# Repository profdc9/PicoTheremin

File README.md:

This is a theremin based on the "Bluepill" devboard with a STM32F103C8T6 microcontroller.
This material is copyrighted by Daniel Marks (KW4TI) and licensed under
the Creative Commons License CC-BY-SA 4.0.  Software is copyrighted using the zlib
open-source license.

It consists of three parts: 

MCTheremin directory - the stm32duino project

board - the PCB board in Kicad of the theremin.

genwaves - little octave script to generate the waveform data

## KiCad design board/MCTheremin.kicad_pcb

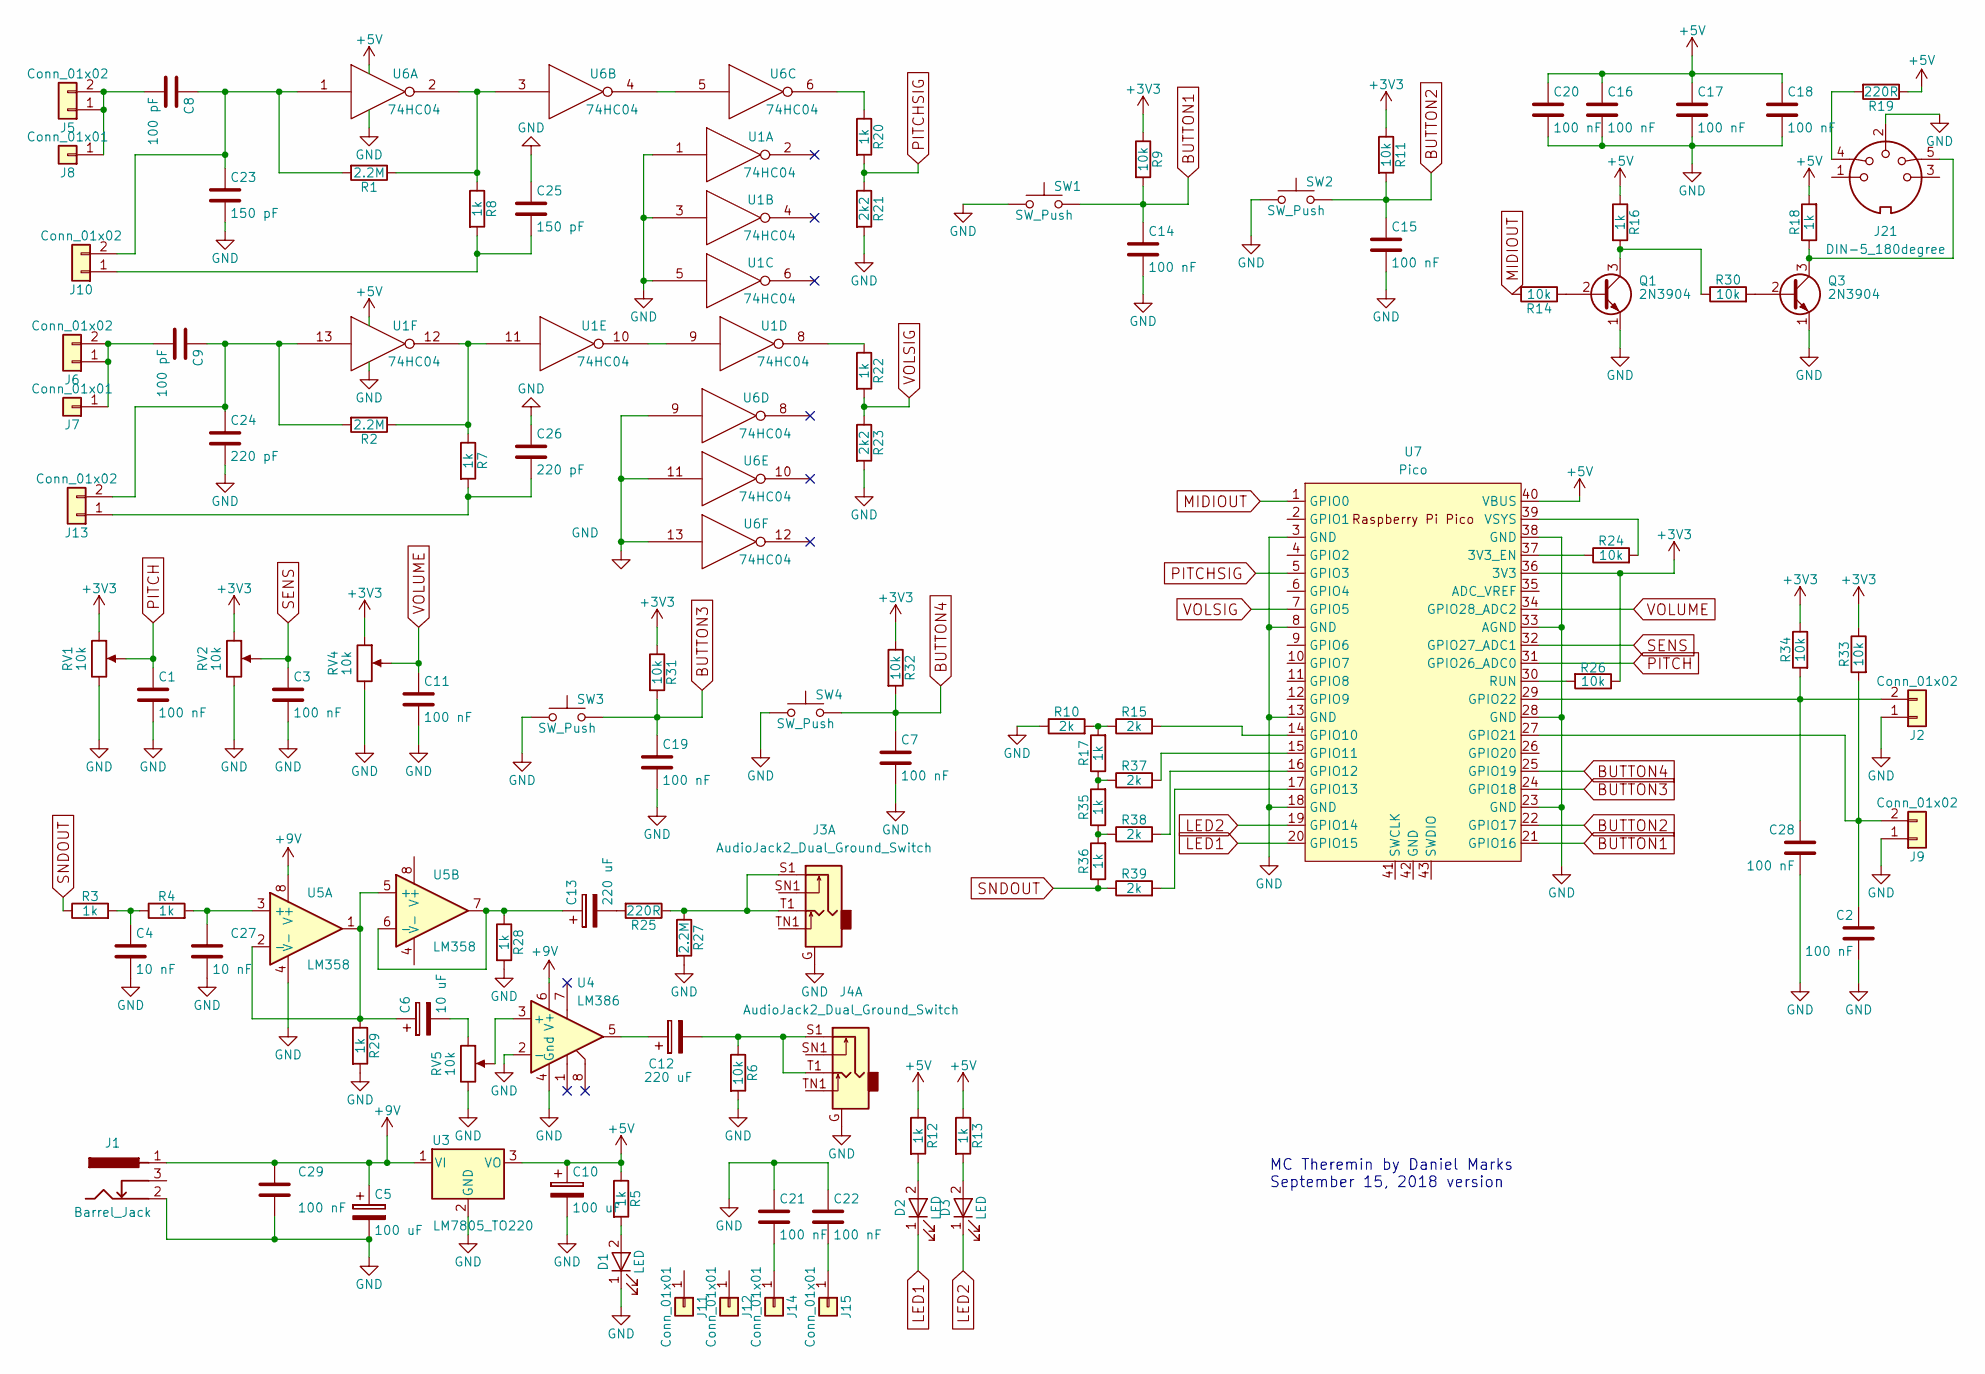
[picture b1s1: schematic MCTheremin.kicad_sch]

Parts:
C1, C2, C3, C7, C11, C14, C15, C16, C17, C18, C19, C20, C21, C22, C28, C29: 100 nF; C_Disc_D5.0mm_W2.5mm_P5.00mm
C4, C27: 10 nF; C_Disc_D5.0mm_W2.5mm_P5.00mm
C5, C10: 100 uF; CP_Radial_D5.0mm_P2.50mm
C6: 10 uF; CP_Radial_D5.0mm_P2.50mm
C8, C9: 100 pF; C_Disc_D5.0mm_W2.5mm_P5.00mm
C12, C13: 220 uF; CP_Radial_D5.0mm_P2.50mm
C23, C25: 150 pF; C_Disc_D5.0mm_W2.5mm_P5.00mm
C24, C26: 220 pF; C_Disc_D5.0mm_W2.5mm_P5.00mm
D1, D2, D3: LED; LED_D5.0mm
J1: Barrel_Jack; BARREL_JACK
J2, J5, J6, J9, J10, J13: Conn_01x02; TerminalBlock_bornier-2_P5.08mm
J3, J4: AudioJack2_Dual_Ground_Switch; PJ-3240-35mm-stereo
J7, J8, J11, J12, J14, J15: Conn_01x01; 1pin
J21: DIN-5_180degree; DIN5Circular
Q1, Q3: 2N3904; TO-92_Inline_Wide
R1, R2, R27: 2.2M; R_Axial_DIN0207_L6.3mm_D2.5mm_P7.62mm_Horizontal
R3, R4, R5, R7, R8, R12, R13, R16, R17, R18, R20, R22, R28, R29, R35, R36: 1k; R_Axial_DIN0207_L6.3mm_D2.5mm_P7.62mm_Horizontal
R6, R9, R11, R14, R24, R26, R30, R31, R32, R33, R34: 10k; R_Axial_DIN0207_L6.3mm_D2.5mm_P7.62mm_Horizontal
R10, R15, R37, R38, R39: 2k; R_Axial_DIN0207_L6.3mm_D2.5mm_P7.62mm_Horizontal
R19, R25: 220R; R_Axial_DIN0207_L6.3mm_D2.5mm_P7.62mm_Horizontal
R21, R23: 2k2; R_Axial_DIN0207_L6.3mm_D2.5mm_P7.62mm_Horizontal
RV1, RV2, RV4, RV5: 10k; Potentiometer_Big_Small_Combined
SW1, SW2, SW3, SW4: SW_Push; SW_PUSH_6mm
U1, U6: 74HC04; DIP-14_W7.62mm_Socket
U3: LM7805_TO220; TO-220-3_Vertical
U4: LM386; DIP-8_W7.62mm_Socket
U5: LM358; DIP-8_W7.62mm_Socket
U7: Pico; RPi_Pico_SMD_TH

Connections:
+3V3: R9.1, R11.1, R26.1, R31.1, R32.1, R33.1, R34.1, RV1.1, RV2.1, RV4.1, U7.36 (3V3)
+5V: C10.1, C16.1, C17.1, C18.1, C20.1, R5.1, R12.1, R13.1, R16.1, R18.2, R19.1, U1.14 (VCC), U3.3 (VO), U6.14 (VCC), U7.40 (VBUS)
+9V: C5.1, C29.1, J1.1, U3.1 (VI), U4.6 (V+), U5.8 (V+)
BUTTON1: C14.1, R9.2, SW1.2, U7.21 (GPIO16)
BUTTON2: C15.1, R11.2, SW2.2, U7.22 (GPIO17)
BUTTON3: C19.1, R31.2, SW3.2, U7.24 (GPIO18)
BUTTON4: C7.1, R32.2, SW4.2, U7.25 (GPIO19)
GND: C1.2, C2.2, C3.2, C4.2, C5.2, C7.2, C10.2, C11.2, C14.2, C15.2, C16.2, C17.2, C18.2, C19.2, C20.2, C21.1, C22.1, C23.2, C24.2, C25.1, C26.1, C27.2, C28.2, C29.2, D1.1 (K), J1.2, J2.1, J3.G, J4.G, J9.1, J21.2, Q1.1 (E), Q3.1 (E), R6.2, R10.1, R21.2, R23.2, R27.2, R28.2, R29.2, RV1.3, RV2.3, RV4.3, RV5.3, SW1.1, SW2.1, SW3.1, SW4.1, U1.1, U1.3, U1.5, U1.7 (GND), U3.2 (GND), U4.2 (-), U4.4 (Gnd), U5.4 (V-), U6.7 (GND), U6.9, U6.11, U6.13, U7.3 (GND), U7.8 (GND), U7.13 (GND), U7.18 (GND), U7.23 (GND), U7.28 (GND), U7.33 (AGND), U7.38 (GND)
LED1: D2.1 (K), U7.20 (GPIO15)
LED2: D3.1 (K), U7.19 (GPIO14)
MIDIOUT: R14.2, U7.1 (GPIO0)
unnamed: C4.1, R3.2, R4.1
unnamed: C6.2, RV5.1
unnamed: C12.1, U4.5
unnamed: C12.2, J4.S1, J4.T1, R6.1
unnamed: C13.2, R25.2
unnamed: D1.2 (A), R5.2
unnamed: D2.2 (A), R12.2
unnamed: D3.2 (A), R13.2
unnamed: C28.1, J2.2, R34.2, U7.29 (GPIO22)
unnamed: J3.S1, J3.T1, R25.1, R27.1
unnamed: C8.2, J5.1, J5.2, J8.1
unnamed: C9.2, J6.1, J6.2, J7.1
unnamed: C2.1, J9.2, R33.2, U7.27 (GPIO21)
unnamed: C25.2, J10.1, R8.2
unnamed: C8.1, C23.1, J10.2, R1.2, U6.1
unnamed: C26.2, J13.1, R7.2
unnamed: C9.1, C24.1, J13.2, R2.2, U1.13
unnamed: C21.2, J14.1
unnamed: C22.2, J15.1
unnamed: J21.4, R19.2
unnamed: Q1.2 (B), R14.1
unnamed: Q1.3 (C), R16.2, R30.1
unnamed: Q3.2 (B), R30.2
unnamed: J21.5, Q3.3 (C), R18.1
unnamed: R1.1, R8.1, U6.2, U6.3
unnamed: R2.1, R7.1, U1.11, U1.12
unnamed: R10.2, R15.1, R17.2
unnamed: R17.1, R35.2, R37.1
unnamed: R20.1, U6.6
unnamed: R22.1, U1.8
unnamed: R35.1, R36.2, R38.1
unnamed: U1.9, U1.10
unnamed: RV5.2, U4.3 (+)
unnamed: C27.1, R4.2, U5.3 (+)
unnamed: C6.1, R29.1, U5.1, U5.2 (-), U5.5 (+)
unnamed: C13.1, R28.1, U5.6 (-), U5.7
unnamed: U6.4, U6.5
unnamed: R24.1, U7.37 (3V3_EN)
unnamed: R15.2, U7.14 (GPIO10)
unnamed: R37.2, U7.15 (GPIO11)
unnamed: R38.2, U7.16 (GPIO12)
unnamed: R39.2, U7.17 (GPIO13)
unnamed: R26.2, U7.30 (RUN)
unnamed: R24.2, U7.39 (VSYS)
PITCH: C1.1, RV1.2, U7.31 (GPIO26_ADC0)
PITCHSIG: R20.2, R21.1, U7.5 (GPIO3)
SENS: C3.1, RV2.2, U7.32 (GPIO27_ADC1)
SNDOUT: R3.1, R36.1, R39.1
VOLSIG: R22.2, R23.1, U7.7 (GPIO5)
VOLUME: C11.1, RV4.2, U7.34 (GPIO28_ADC2)

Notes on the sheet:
MC Theremin by Daniel Marks September 15, 2018 version

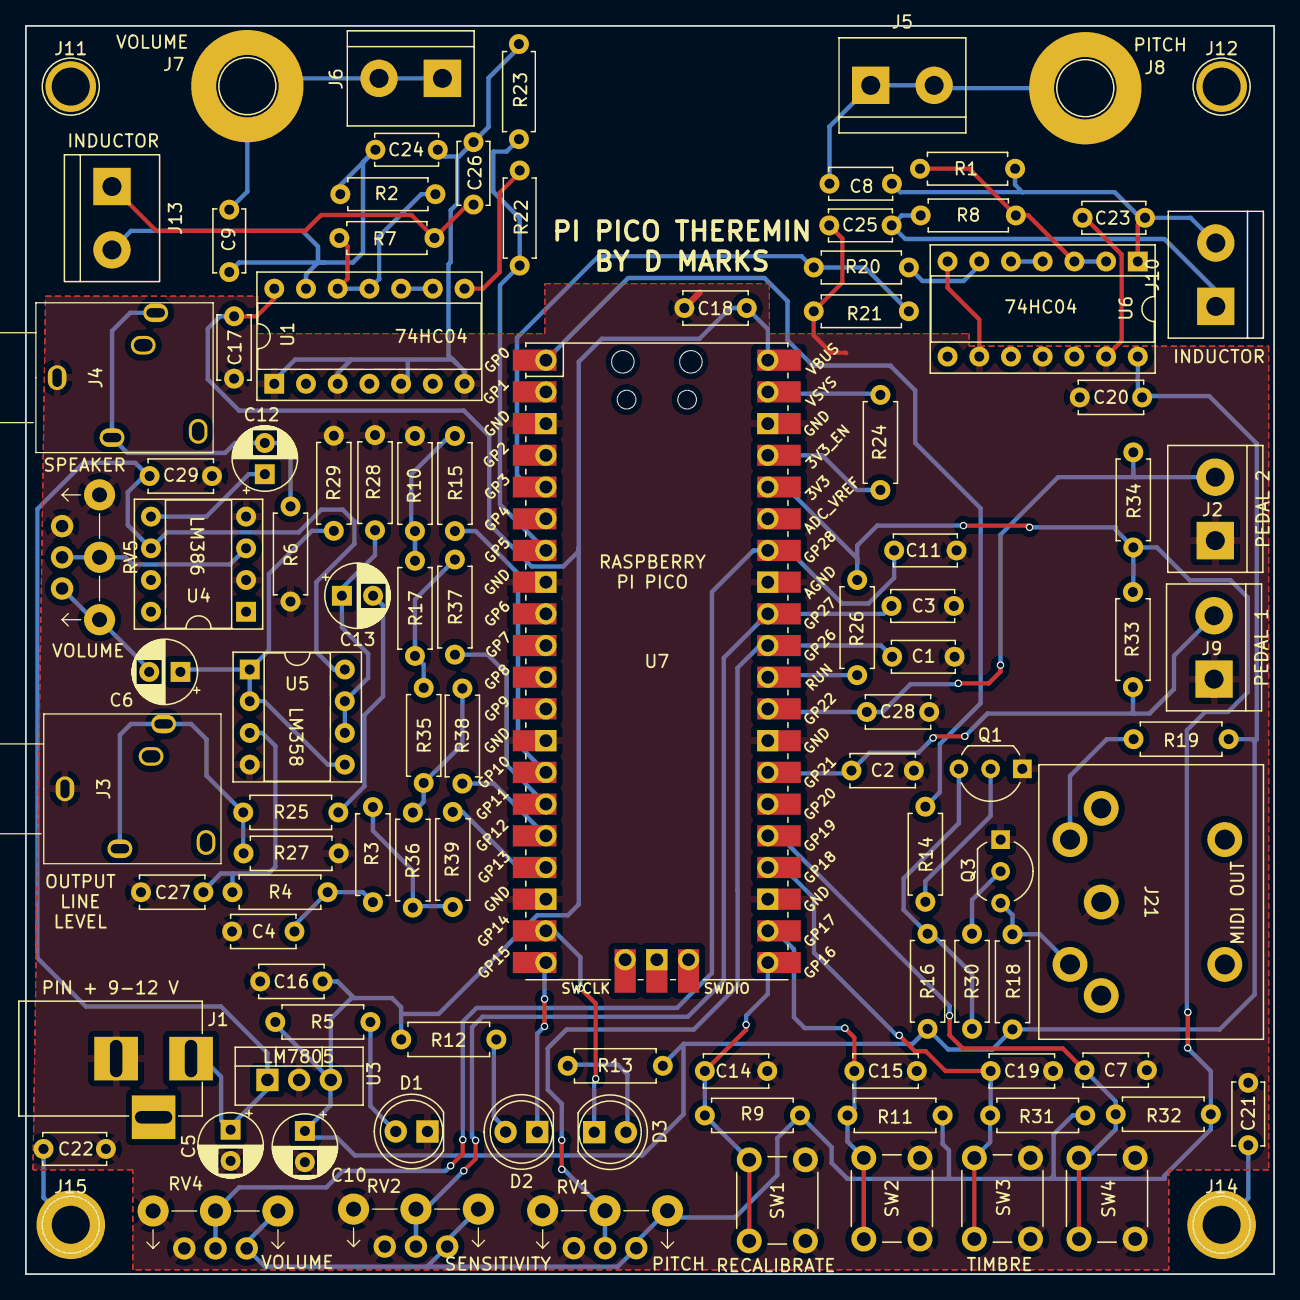
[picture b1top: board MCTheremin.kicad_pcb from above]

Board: 2 copper layers, 100.0 x 100.0 mm, 103 parts (0 on the bottom side), 61 nets.

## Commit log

2025-01-11 Added external inductor support
2025-02-15 Fixed layout
